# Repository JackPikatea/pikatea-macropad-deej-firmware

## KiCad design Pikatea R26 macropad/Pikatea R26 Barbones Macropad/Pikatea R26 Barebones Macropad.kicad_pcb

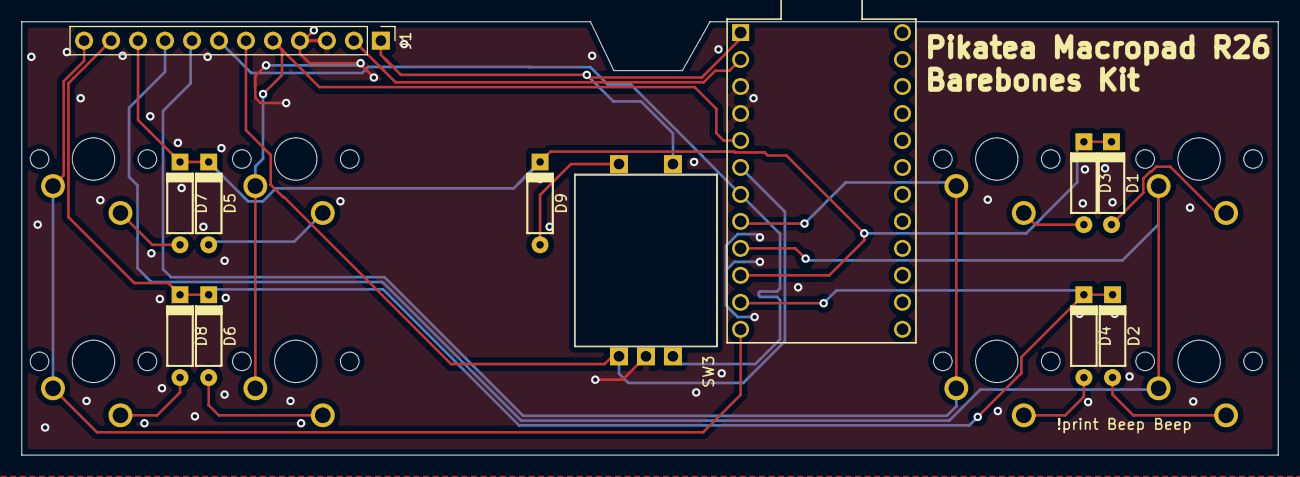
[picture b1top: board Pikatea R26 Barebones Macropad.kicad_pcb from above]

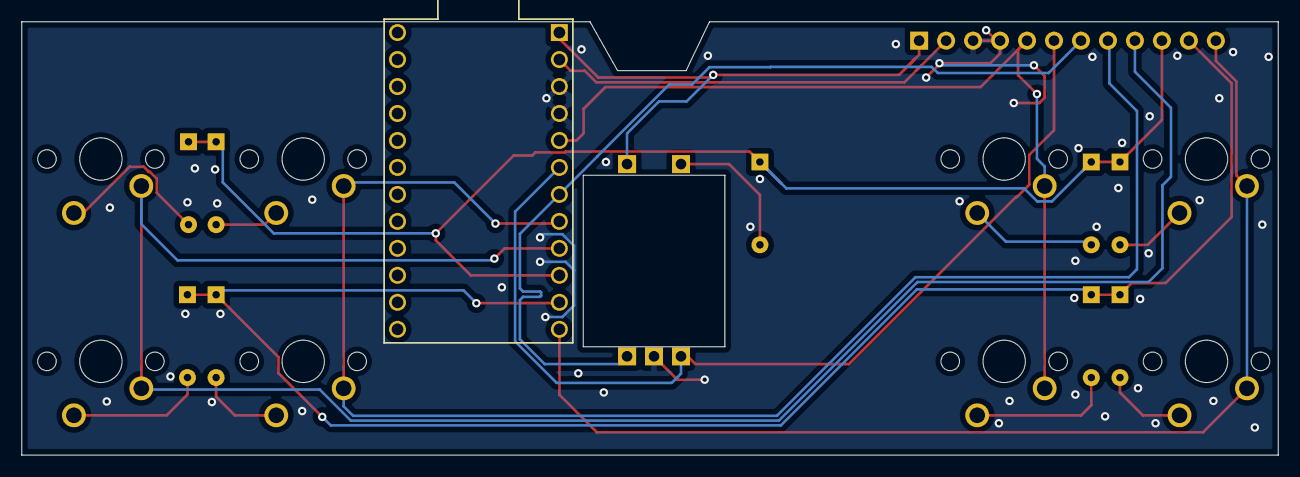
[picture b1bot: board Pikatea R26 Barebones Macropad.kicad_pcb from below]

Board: 2 copper layers, 118.3 x 40.8 mm, 20 parts (8 on the bottom side), 20 nets.

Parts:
D1, D2, D3, D4, D5, D6, D7, D8, D9: 1N4148W; D_axial
J1: Conn_01x12_Female; PinHeader_1x12_P2.54mm_Vertical
MX1, MX2, MX3, MX4, MX5, MX6, MX7, MX8: MX-LED; MXOnly-1U-NoLED
SW3: Rotary_Encoder_Switch; Encoder-BI_EN11_HSM0E
U1: ProMicro

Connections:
/A: J1.7, SW3.A, U1.7
/A0: D2.1, D4.1, D6.1, D8.1, J1.11, U1.11
/A3: D1.1, D3.1, D5.1, D7.1, D9.1, J1.10, U1.10
/A4: J1.12, MX4.1, MX8.1, U1.12
/A10: J1.1, SW3.S2, U1.1
/B: J1.6, SW3.B, U1.6
/D7: J1.8, MX2.1, MX6.1, U1.8
/D8: J1.5, MX3.1, MX7.1, U1.5
/D9: J1.9, MX1.1, MX5.1, U1.9
GND: J1.3, J1.4, SW3.C, U1.3, U1.4
unnamed: D1.2, MX5.2
unnamed: D2.2, MX1.2
unnamed: D3.2, MX6.2
unnamed: D4.2, MX2.2
unnamed: D5.2, MX7.2
unnamed: D6.2, MX3.2
unnamed: D7.2, MX8.2
unnamed: D8.2, MX4.2
unnamed: D9.2, SW3.S1
unnamed: J1.2, U1.2

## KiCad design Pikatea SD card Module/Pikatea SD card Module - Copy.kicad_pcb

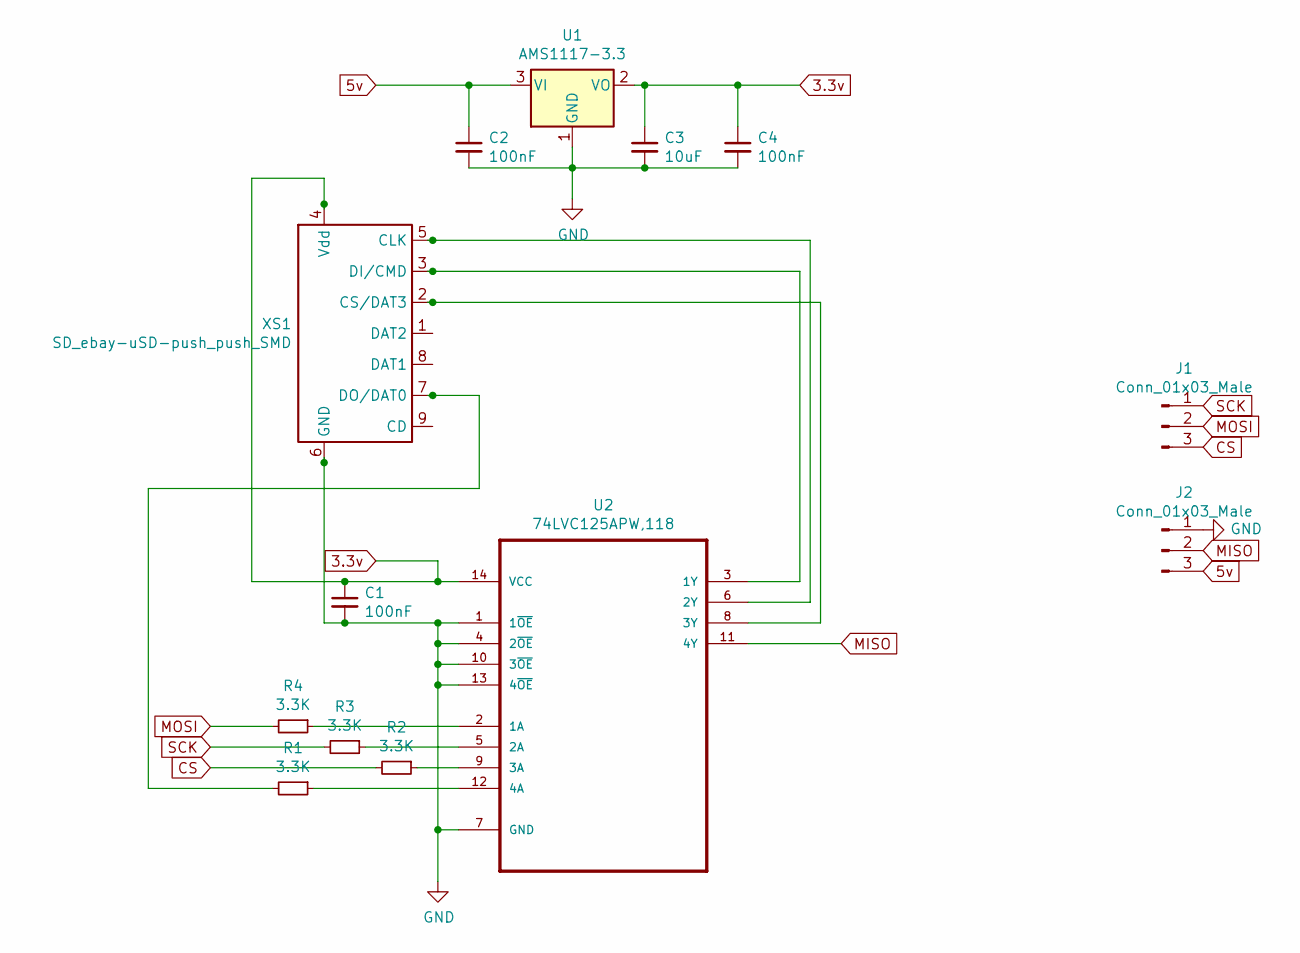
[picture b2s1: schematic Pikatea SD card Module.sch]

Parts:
C1, C2, C4: 100nF; C_0805_2012Metric
C3: 10uF; C_0805_2012Metric
J1, J2: Conn_01x03_Male; PinHeader_1x03_P2.54mm_Vertical
R1, R2, R3, R4: 3.3K; R_0805_2012Metric
U1: AMS1117-3.3; SOT-223-3_TabPin2
U2: 74LVC125APW,118; TSSOP-14-1EP_4.4x5mm_P0.65mm
XS1: SD_ebay-uSD-push_push_SMD; Conn_uSDcard

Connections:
3.3v: C1.1, C3.1, C4.1, U1.2 (VO), U2.14 (VCC), XS1.4 (Vdd)
5v: C2.1, J2.3, U1.3 (VI)
CS: J1.3, R2.2
GND: C1.2, C2.2, C3.2, C4.2, J2.1, U1.1 (GND), U2.1 (1~OE), U2.4 (2~OE), U2.7 (GND), U2.10 (3~OE), U2.13 (4~OE), XS1.6 (GND)
MISO: J2.2, U2.11 (4Y)
MOSI: J1.2, R4.2
unnamed: R1.1, U2.12 (4A)
unnamed: R1.2, XS1.7 (DO/DAT0)
unnamed: R2.1, U2.9 (3A)
unnamed: R3.1, U2.5 (2A)
unnamed: R4.1, U2.2 (1A)
unnamed: U2.3 (1Y), XS1.3 (DI/CMD)
unnamed: U2.6 (2Y), XS1.5 (CLK)
unnamed: U2.8 (3Y), XS1.2 (CS/DAT3)
SCK: J1.1, R3.2

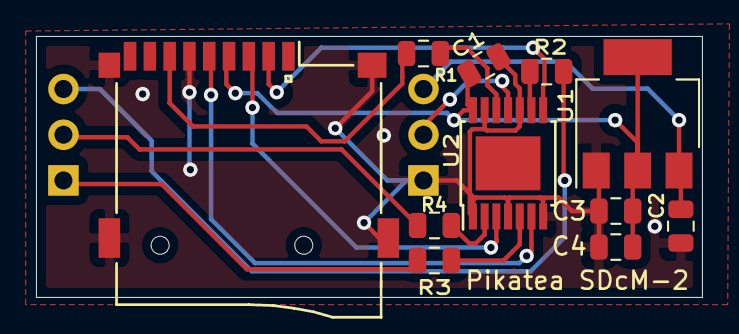
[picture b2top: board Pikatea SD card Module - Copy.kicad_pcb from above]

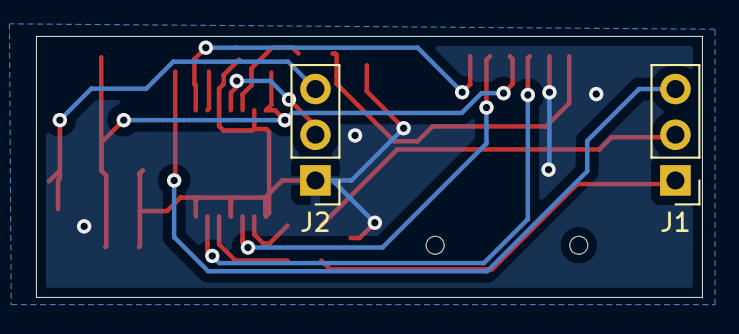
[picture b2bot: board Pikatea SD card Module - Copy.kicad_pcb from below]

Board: 2 copper layers, 37.0 x 14.5 mm, 13 parts (2 on the bottom side), 15 nets.

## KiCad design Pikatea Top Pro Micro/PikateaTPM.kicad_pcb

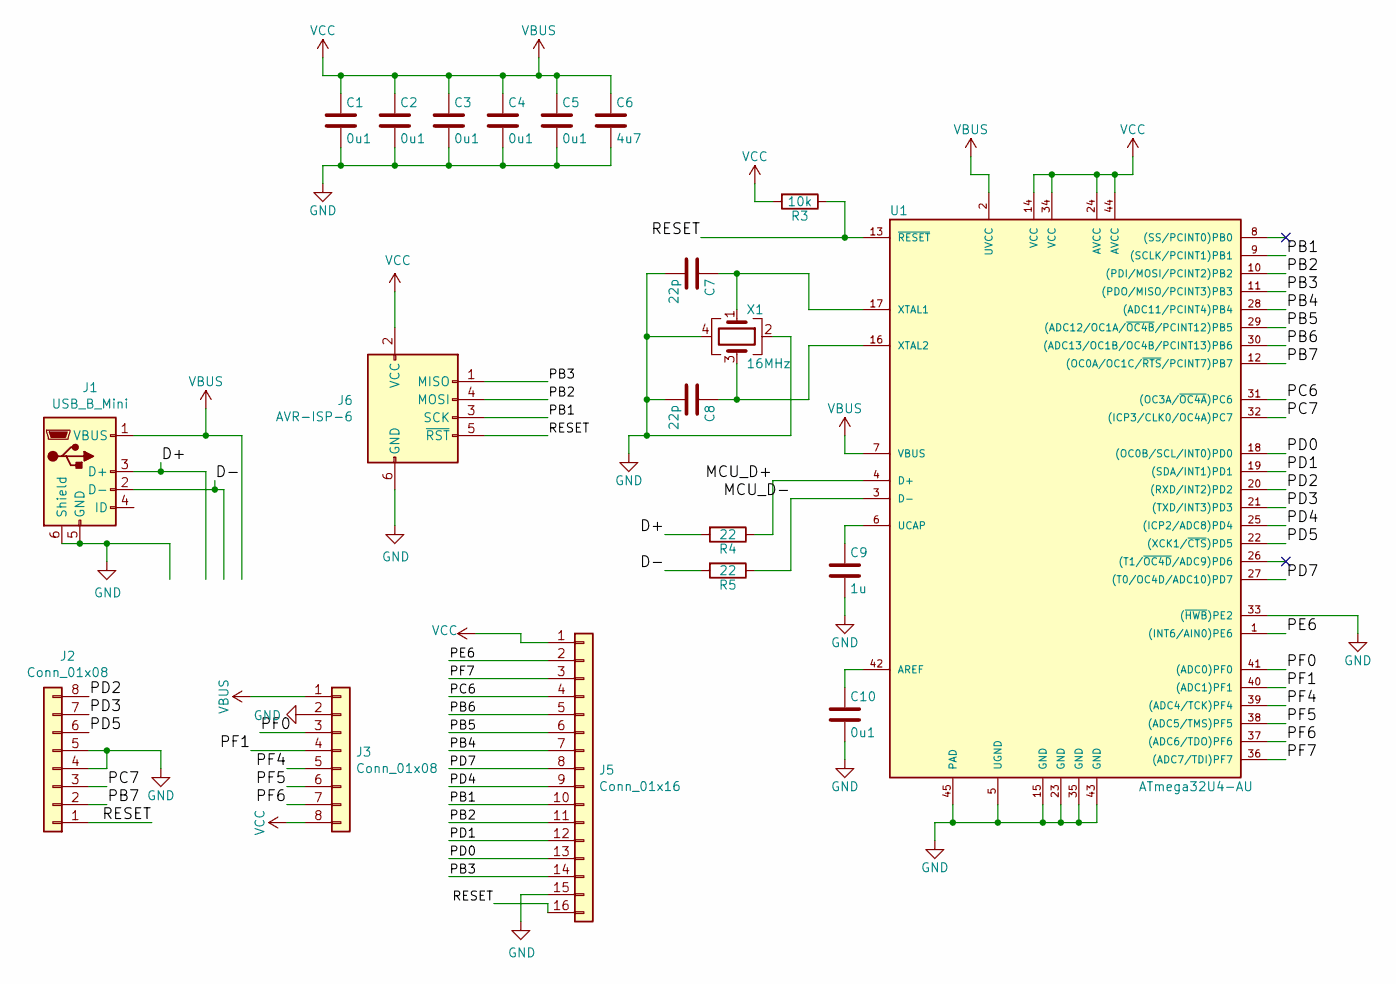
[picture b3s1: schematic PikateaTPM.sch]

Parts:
C1, C2, C3, C4, C5, C10: 0u1; C_0805_2012Metric; LCSC C1525
C6: 4u7; C_0805_2012Metric; LCSC C23733
C7, C8: 22p; C_0805_2012Metric; LCSC C1555
C9: 1u; C_0805_2012Metric; LCSC C52923
J1: USB_B_Mini; USB-Mini-B_ LCSC-C46398; LCSC C46398
J2, J3: Conn_01x08; PinHeader_1x08_P2.54mm_Vertical
J5: Conn_01x16; PinHeader_1x16_P2.54mm_Vertical
J6: AVR-ISP-6; IDC-Header_2x03_P2.54mm_Vertical
R3: 10k; R_0805_2012Metric; LCSC C25744
R4, R5: 22; R_0805_2012Metric; LCSC C25092
U1: ATmega32U4-AU; TQFP-44_10x10mm_P0.8mm; LCSC C44854
X1: 16MHz; Crystal_SMD_SeikoEpson_FA238-4Pin_3.2x2.5mm; LCSC C13738

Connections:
/D+: J1.3 (D+), R4.2
/D-: J1.2 (D-), R5.2
/MCU_D+: R4.1, U1.4 (D+)
/MCU_D-: R5.1, U1.3 (D-)
/PB1: J5.10, J6.3 (SCK), U1.9 ((SCLK/PCINT1)PB1)
/PB2: J5.11, J6.4 (MOSI), U1.10 ((PDI/MOSI/PCINT2)PB2)
/PB3: J5.14, J6.1 (MISO), U1.11 ((PDO/MISO/PCINT3)PB3)
/PB4: J5.7, U1.28 ((ADC11/PCINT4)PB4)
/PB5: J5.6, U1.29 ((ADC12/OC1A/~OC4B~/PCINT12)PB5)
/PB6: J5.5, U1.30 ((ADC13/OC1B/OC4B/PCINT13)PB6)
/PB7: J2.2, U1.12 ((OC0A/OC1C/~RTS~/PCINT7)PB7)
/PC6: J5.4, U1.31 ((OC3A/~OC4A~)PC6)
/PC7: J2.3, U1.32 ((ICP3/CLK0/OC4A)PC7)
/PD0: J5.13, U1.18 ((OC0B/SCL/INT0)PD0)
/PD1: J5.12, U1.19 ((SDA/INT1)PD1)
/PD2: J2.8, U1.20 ((RXD/INT2)PD2)
/PD3: J2.7, U1.21 ((TXD/INT3)PD3)
/PD4: J5.9, U1.25 ((ICP2/ADC8)PD4)
/PD5: J2.6, U1.22 ((XCK1/~CTS~)PD5)
/PD7: J5.8, U1.27 ((T0/OC4D/ADC10)PD7)
/PE6: J5.2, U1.1 ((INT6/AIN0)PE6)
/PF0: J3.3, U1.41 ((ADC0)PF0)
/PF1: J3.4, U1.40 ((ADC1)PF1)
/PF4: J3.5, U1.39 ((ADC4/TCK)PF4)
/PF5: J3.6, U1.38 ((ADC5/TMS)PF5)
/PF6: J3.7, U1.37 ((ADC6/TDO)PF6)
/PF7: J5.3, U1.36 ((ADC7/TDI)PF7)
/RESET: J2.1, J5.16, J6.5 (~RST), R3.1, U1.13 (~RESET~)
GND: C1.2, C2.2, C3.2, C4.2, C5.2, C6.2, C7.2, C8.2, C9.2, C10.2, J1.5 (GND), J1.6 (Shield), J2.4, J2.5, J3.2, J5.15, J6.6 (GND), U1.5 (UGND), U1.15 (GND), U1.23 (GND), U1.33 ((~HWB~)PE2), U1.35 (GND), U1.43 (GND), U1.45 (PAD), X1.2, X1.4
unnamed: C7.1, U1.17 (XTAL1), X1.1
unnamed: C8.1, U1.16 (XTAL2), X1.3
unnamed: C9.1, U1.6 (UCAP)
unnamed: C10.1, U1.42 (AREF)
VBUS: C1.1, C2.1, C3.1, C4.1, C5.1, C6.1, J1.1 (VBUS), J3.1, J3.8, J5.1, J6.2 (VCC), R3.2, U1.2 (UVCC), U1.7 (VBUS), U1.14 (VCC), U1.24 (AVCC), U1.34 (VCC), U1.44 (AVCC)

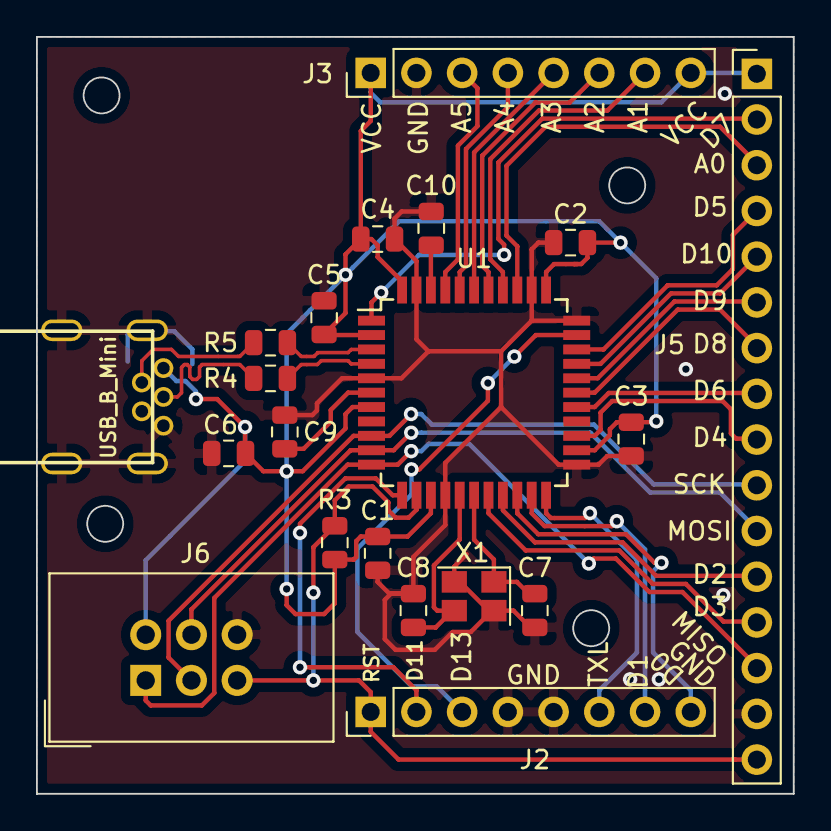
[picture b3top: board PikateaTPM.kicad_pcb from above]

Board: 2 copper layers, 42.0 x 42.1 mm, 20 parts (0 on the bottom side), 34 nets.

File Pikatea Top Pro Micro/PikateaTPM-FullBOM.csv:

Source:,,,,,,
Date:,8/27/2020 6:38:08 PM,,,,,
Tool:,Eeschema (5.1.6)-1,,,,,
Component Count:,20,,,,,
Ref,Value,Footprint,Manufacturer,Manufacturer Part Number,Digikey part number,Description
C1,0.1uF,Capacitor_SMD:C_0805_2012Metric,Samsung Electro-Mechanics,CL21B104KACNFNC,1276-2442-2-ND,0.1µF ±10% 25V Ceramic Capacitor X7R 0805 (2012 Metric)
C2,0.1uF,Capacitor_SMD:C_0805_2012Metric,Samsung Electro-Mechanics,CL21B104KACNFNC,1276-2442-2-ND,0.1µF ±10% 25V Ceramic Capacitor X7R 0805 (2012 Metric)
C3,0.1uF,Capacitor_SMD:C_0805_2012Metric,Samsung Electro-Mechanics,CL21B104KACNFNC,1276-2442-2-ND,0.1µF ±10% 25V Ceramic Capacitor X7R 0805 (2012 Metric)
C4,0.1uF,Capacitor_SMD:C_0805_2012Metric,Samsung Electro-Mechanics,CL21B104KACNFNC,1276-2442-2-ND,0.1µF ±10% 25V Ceramic Capacitor X7R 0805 (2012 Metric)
C5,0.1uF,Capacitor_SMD:C_0805_2012Metric,Samsung Electro-Mechanics,CL21B104KACNFNC,1276-2442-2-ND,0.1µF ±10% 25V Ceramic Capacitor X7R 0805 (2012 Metric)
C6,4.7uF,Capacitor_SMD:C_0805_2012Metric,Samsung Electro-Mechanics,CL21A475KPFNNNF,CL21A475KPFNNNF-ND,4.7µF ±10% 10V Ceramic Capacitor X5R 0805 (2012 Metric)
C7,22pF,Capacitor_SMD:C_0805_2012Metric,KEMET,C0805C220J5GACTU,399-1113-2-ND,"22pF ±5% 50V Ceramic Capacitor C0G, NP0 0805 (2012 Metric)"
C8,22pF,Capacitor_SMD:C_0805_2012Metric,KEMET,C0805C220J5GACTU,399-1113-2-ND,"22pF ±5% 50V Ceramic Capacitor C0G, NP0 0805 (2012 Metric)"
C9,1uF,Capacitor_SMD:C_0805_2012Metric,Samsung Electro-Mechanics,CL21B105KPFNNNG,CL21B105KPFNNNG-ND,1µF ±10% 10V Ceramic Capacitor X7R 0805 (2012 Metric)
C10,0.1uF,Capacitor_SMD:C_0805_2012Metric,Samsung Electro-Mechanics,CL21B104KACNFNC,1276-2442-2-ND,0.1µF ±10% 25V Ceramic Capacitor X7R 0805 (2012 Metric)
J1,USB_B_Mini,usb_mini:USB-Mini-B_ LCSC-C46398,Jing Extension(???),MINI-5P-90-LCP,,
R3,10k,Resistor_SMD:R_0805_2012Metric,Yageo,RC0805FR-0710KL,311-10.0KCRTR-ND,"10 kOhms ±1% 0.125W, 1/8W Chip Resistor 0805"
R4,22,Resistor_SMD:R_0805_2012Metric,TE Connectivity Passive Product,CRG0805F22R,A126352TR-ND,
R5,22,Resistor_SMD:R_0805_2012Metric,TE Connectivity Passive Product,CRG0805F22R,A126352TR-ND,
U1,ATmega32U4-AU,Package_QFP:TQFP-44_10x10mm_P0.8mm,Microchip Technology,ATMEGA32U4-AU,ATMEGA32U4-AU-ND,
X1,16MHz,Crystal:Crystal_SMD_SeikoEpson_FA238-4Pin_3.2x2.5mm,Yangxing Tech,X322516MLB4SI,,16MHz ±10ppm 9pF 60?

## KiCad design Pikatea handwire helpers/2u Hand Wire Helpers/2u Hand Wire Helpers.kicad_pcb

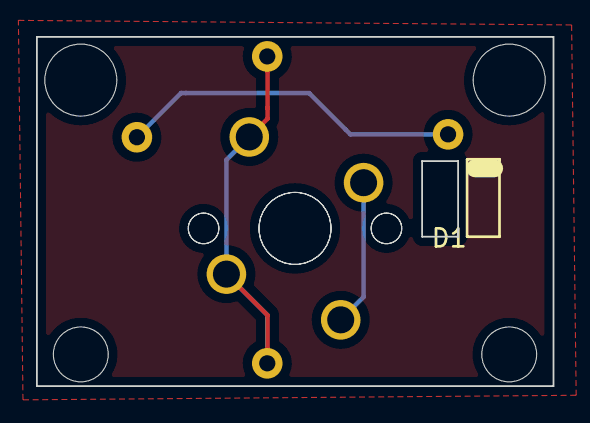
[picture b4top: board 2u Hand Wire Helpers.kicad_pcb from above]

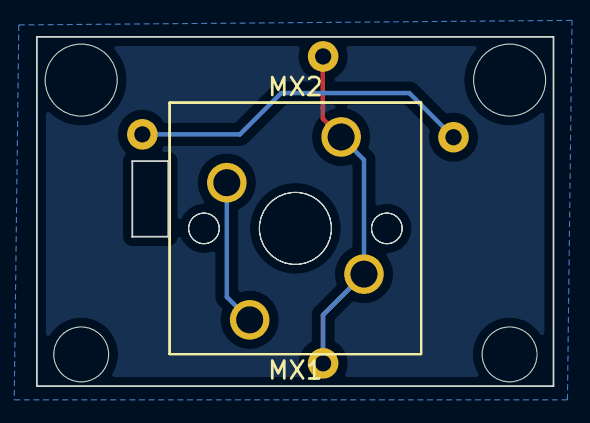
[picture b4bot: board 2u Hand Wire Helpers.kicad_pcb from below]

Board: 2 copper layers, 28.7 x 19.4 mm, 3 parts (2 on the bottom side), 2 nets.

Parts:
D1: DIODE; Diode Handwire helper
MX1: MX-NoLED; SW_Cherry_MX_2.00u_PCB
MX2: MX-NoLED; SW_Cherry_MX_1.00u_PCB

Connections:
unnamed: D1.2, MX1.2, MX2.1
unnamed: MX1.1, MX2.2
